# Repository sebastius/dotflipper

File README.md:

# dotflipper

My Flip Dot controller.

## Status (November 2026)

- **v1** (`hardware-v1`): the original controller, based on the PCA9685 i2c port expanders. Tested and
  working, but dangerous and slow.
- **v3** (`hardware-v3`): a new controller with 74HC595 shift registers, where the hardware keeps plus and
  minus of a wire apart. Designed and on order, not tested yet.
- **Software** (`software`): firmware for v1 and v3, being developed with the help of AI. Try the v3
  firmware in your browser: https://sebastius.github.io/dotflipper/
- **Original software** (`software-original`): the hand-written firmware from 2018-2020, heavily outdated.

## License

CC BY-SA 4.0, except the word clock font derived from Ithaca, which stays under the SIL Open Font License.
Fonts, authors and licenses: [software/tools/fonts](software/tools/fonts/README.md).

lol

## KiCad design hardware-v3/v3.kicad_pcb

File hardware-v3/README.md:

# Controller v3

> **Untested.** The schematic, placement, scripts and part choices were made with an AI assistant
> (Claude); the board was routed by hand in KiCad. The board passes DRC, but none has been built yet.
> Test the first board with a current-limited supply: these drivers switch 20 V coils, and a mistake
> can short them.

One flip dot panel of 32x16 (32 lines on X1, 16 rows on X2/X3) per board, so two boards for a 32x32
display. 205 x 80 mm, two layers, all logic and drivers SMD.

## How it works

- **Drivers:** six groups of eight lines. Each group has two 74HC595s on the same data, one feeding an
  XL62783 (lines to 20 V) and one feeding a ULN2803A (lines to ground). Groups 1-4 drive the 32 lines on
  X1, group 5 rows 0-7 on X3, group 6 rows 8-15 on X2. `bits.csv` lists which bit drives which wire.
- **Protection:** DIR_X1, DIR_ROW and nOE gate the output enables of the 595s through a 74HC32 and
  74HC14, so plus and minus of one line or row can never be on together, also not after a software bug.
  Change DIR only while nOE is high.
- **Chain:** boards chain over a 10-way flat cable, J2 of one board to J3 of the next. Each board
  buffers the incoming signals with a 74AHCT541 (TTL inputs, so the 3.3 V of the ESP32 is enough), and
  the chain data leaves through a 74LVC1G79 on the falling SCLK edge. Close JP1 on the last board: the
  chain data then returns over RET to the ESP32 (IO13, through R4/R5 to 3.3 V) so the firmware can read
  the chain back.
- **ESP32:** one ESP32-S3-DevKitC-1 (A1) drives all boards; on the other boards A1 stays empty.
  DATA IO11, SCLK IO12, LATCH IO10, nOE IO9, DIR_X1 IO14, DIR_ROW IO8, return IO13, coil current IO4.
- **Coil current:** all ULN2803As return to ground through a 0.1 ohm shunt (R8). An INA180A2 measures
  it; R6/R7 scale 0.45 A to 1.5 V for IO4. TP1 brings the same signal out on boards without an ESP32.
- **Power:** 20 V in on J4, J5 passes it on to the next board. 3 A fuse F1, 220 uF bulk capacitor C15.
  An AP63205 buck makes 5 V for the logic and, through D1, for the ESP32 (D1 keeps USB power on the
  ESP32 from feeding the board).

## Files

- `generate.py`: makes the schematic and brings the board up to date; placement and tracks stay.
  `--opnieuw` throws the board away and places everything again.
- `export_jlc.py`: Gerbers, drill files, BOM and CPL for JLCPCB in `jlcpcb/`. It refuses to run while
  DRC finds errors, open connections or differences with the schematic.
- `jlcpcb/`: the production files of the current board. Through-hole parts (connectors, headers,
  terminals, the ESP32) are not in the BOM; order and solder them yourself.
- `v3.kicad_dru`: design rules for JLCPCB standard 2-layer 1 oz boards.
- `bits.csv`: which bit of the chain drives which wire, for the firmware.

## Not yet verified on hardware

- Coil peak current: estimated 450-480 mA, the drivers are rated 390-400 mA recommended, 500 mA absolute.
- The ESP32 footprint: print it 1:1 and lay the module on it, clones are not always the same.
- The buck regulator layout.
- The part rotations in the CPL, checked only in the JLC preview.

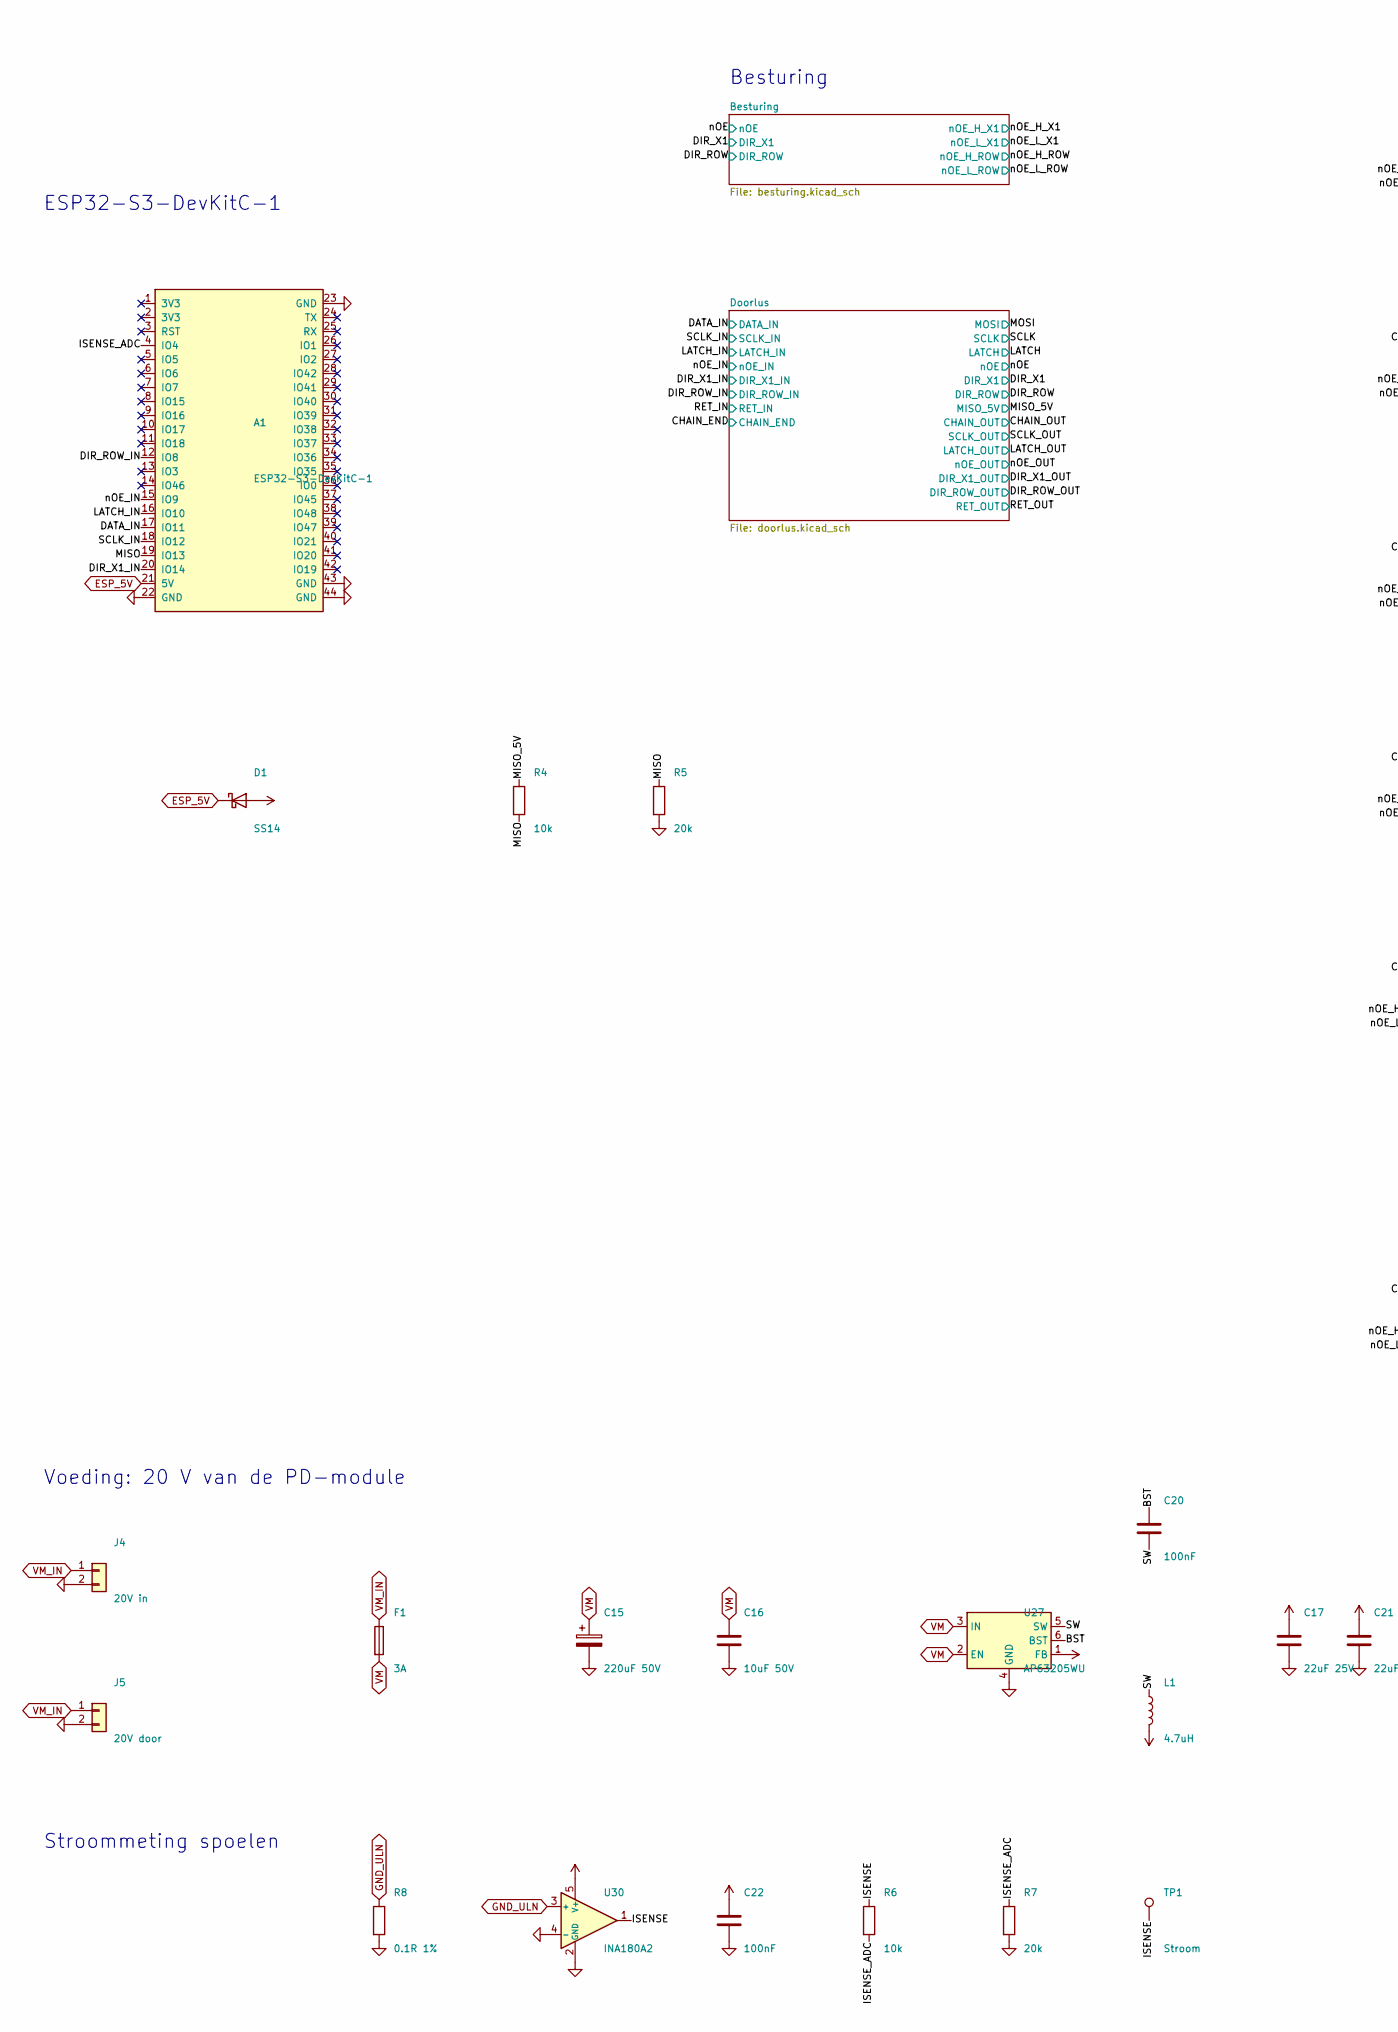
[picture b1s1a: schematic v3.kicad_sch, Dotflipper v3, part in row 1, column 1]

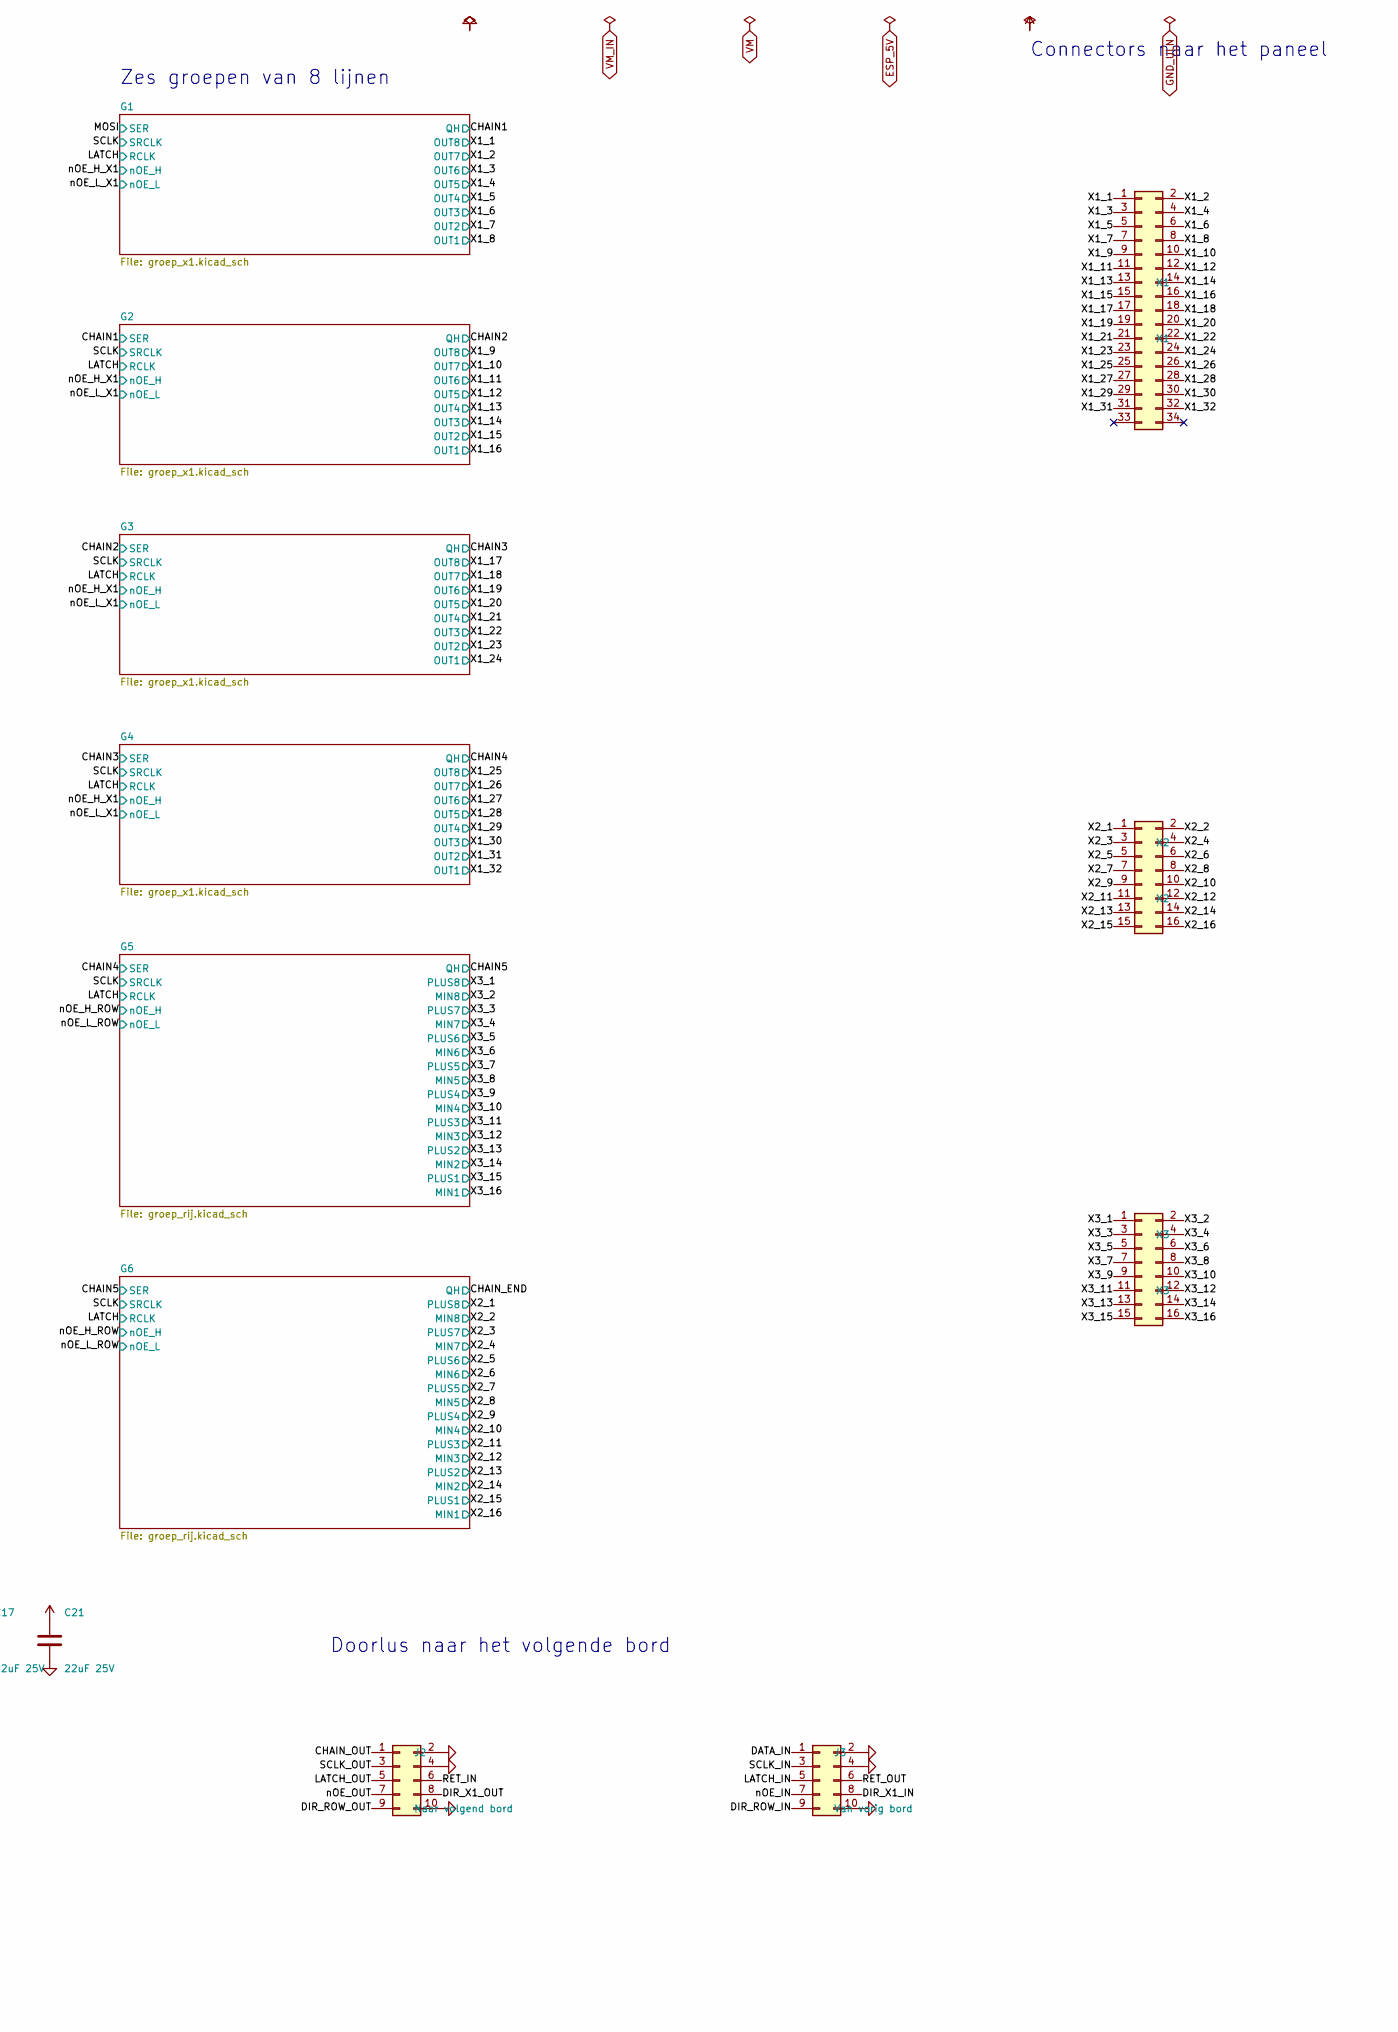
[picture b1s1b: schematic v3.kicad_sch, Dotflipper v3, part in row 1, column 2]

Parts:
A1: ESP32-S3-DevKitC-1
C15: 220uF 50V; CP_Elec_10x10.5; LCSC C46550417
C16: 10uF 50V; C_1206_3216Metric; LCSC C13585
C17, C21: 22uF 25V; C_1206_3216Metric; LCSC C12891
C20, C22: 100nF; C_0603_1608Metric; LCSC C14663
D1: SS14; D_SMA; LCSC C2480
F1: 3A; Fuse_1206_3216Metric; LCSC C182445
J2: Naar volgend bord; IDC-Header_2x05_P2.54mm_Vertical
J3: Van vorig bord; IDC-Header_2x05_P2.54mm_Vertical
J4: 20V in; TerminalBlock_Phoenix_MKDS-1,5-2-5.08_1x02_P5.08mm_Horizont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
J5: 20V door; TerminalBlock_Phoenix_MKDS-1,5-2-5.08_1x02_P5.08mm_Horizont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
L1: 4.7uH; L_Sunlord_SWPA4030S; LCSC C57269
R4, R6: 10k; R_0603_1608Metric; LCSC C25804
R5, R7: 20k; R_0603_1608Metric; LCSC C4184
R8: 0.1R 1%; R_1206_3216Metric; LCSC C25334
TP1: Stroom; TestPoint_Pad_D1.5mm
U27: AP63205WU; TSOT-23-6; LCSC C2071056
U30: INA180A2; SOT-23-5; LCSC C192764
X1: X1; IDC-Header_2x17_P2.54mm_Vertical
X2: X2; IDC-Header_2x08_P2.54mm_Vertical
X3: X3; IDC-Header_2x08_P2.54mm_Vertical

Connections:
+5V: C17.1, C21.1, C22.1, D1.2 (A), L1.2, U27.1 (FB), U30.5 (V+); also elsewhere on the board
/BST: C20.1, U27.6 (BST)
/CHAIN_OUT: J2.1; also elsewhere on the board
/DATA_IN: A1.17 (IO11), J3.1; also elsewhere on the board
/DIR_ROW_IN: A1.12 (IO8), J3.9; also elsewhere on the board
/DIR_ROW_OUT: J2.9; also elsewhere on the board
/DIR_X1_IN: A1.20 (IO14), J3.8; also elsewhere on the board
/DIR_X1_OUT: J2.8; also elsewhere on the board
/ISENSE: R6.1, TP1.1, U30.1
/ISENSE_ADC: A1.4 (IO4), R6.2, R7.1
/LATCH_IN: A1.16 (IO10), J3.5; also elsewhere on the board
/LATCH_OUT: J2.5; also elsewhere on the board
/MISO: A1.19 (IO13), R4.2, R5.1
/MISO_5V: R4.1; also elsewhere on the board
/RET_IN: J2.6; also elsewhere on the board
/RET_OUT: J3.6; also elsewhere on the board
/SCLK_IN: A1.18 (IO12), J3.3; also elsewhere on the board
/SCLK_OUT: J2.3; also elsewhere on the board
/SW: C20.2, L1.1, U27.5 (SW)
/X1_1: X1.1; also elsewhere on the board
/X1_2: X1.2; also elsewhere on the board
/X1_3: X1.3; also elsewhere on the board
/X1_4: X1.4; also elsewhere on the board
/X1_5: X1.5; also elsewhere on the board
/X1_6: X1.6; also elsewhere on the board
/X1_7: X1.7; also elsewhere on the board
/X1_8: X1.8; also elsewhere on the board
/X1_9: X1.9; also elsewhere on the board
/X1_10: X1.10; also elsewhere on the board
/X1_11: X1.11; also elsewhere on the board
/X1_12: X1.12; also elsewhere on the board
/X1_13: X1.13; also elsewhere on the board
/X1_14: X1.14; also elsewhere on the board
/X1_15: X1.15; also elsewhere on the board
/X1_16: X1.16; also elsewhere on the board
/X1_17: X1.17; also elsewhere on the board
/X1_18: X1.18; also elsewhere on the board
/X1_19: X1.19; also elsewhere on the board
/X1_20: X1.20; also elsewhere on the board
/X1_21: X1.21; also elsewhere on the board
/X1_22: X1.22; also elsewhere on the board
/X1_23: X1.23; also elsewhere on the board
/X1_24: X1.24; also elsewhere on the board
/X1_25: X1.25; also elsewhere on the board
/X1_26: X1.26; also elsewhere on the board
/X1_27: X1.27; also elsewhere on the board
/X1_28: X1.28; also elsewhere on the board
/X1_29: X1.29; also elsewhere on the board
/X1_30: X1.30; also elsewhere on the board
/X1_31: X1.31; also elsewhere on the board
/X1_32: X1.32; also elsewhere on the board
/X2_1: X2.1; also elsewhere on the board
/X2_2: X2.2; also elsewhere on the board
/X2_3: X2.3; also elsewhere on the board
/X2_4: X2.4; also elsewhere on the board
/X2_5: X2.5; also elsewhere on the board
/X2_6: X2.6; also elsewhere on the board
/X2_7: X2.7; also elsewhere on the board
/X2_8: X2.8; also elsewhere on the board
/X2_9: X2.9; also elsewhere on the board
/X2_10: X2.10; also elsewhere on the board
/X2_11: X2.11; also elsewhere on the board
/X2_12: X2.12; also elsewhere on the board
/X2_13: X2.13; also elsewhere on the board
/X2_14: X2.14; also elsewhere on the board
/X2_15: X2.15; also elsewhere on the board
/X2_16: X2.16; also elsewhere on the board
/X3_1: X3.1; also elsewhere on the board
/X3_2: X3.2; also elsewhere on the board
/X3_3: X3.3; also elsewhere on the board
/X3_4: X3.4; also elsewhere on the board
/X3_5: X3.5; also elsewhere on the board
/X3_6: X3.6; also elsewhere on the board
/X3_7: X3.7; also elsewhere on the board
/X3_8: X3.8; also elsewhere on the board
/X3_9: X3.9; also elsewhere on the board
/X3_10: X3.10; also elsewhere on the board
/X3_11: X3.11; also elsewhere on the board
/X3_12: X3.12; also elsewhere on the board
/X3_13: X3.13; also elsewhere on the board
/X3_14: X3.14; also elsewhere on the board
/X3_15: X3.15; also elsewhere on the board
/X3_16: X3.16; also elsewhere on the board
/nOE_IN: A1.15 (IO9), J3.7; also elsewhere on the board
/nOE_OUT: J2.7; also elsewhere on the board
ESP_5V: A1.21 (5V), D1.1 (K)
GND: A1.22 (GND), A1.23 (GND), A1.43 (GND), A1.44 (GND), C15.2, C16.2, C17.2, C21.2, C22.2, J2.2, J2.4, J2.10, J3.2, J3.4, J3.10, J4.2, J5.2, R5.2, R7.2, R8.2, U27.4 (GND), U30.2 (GND), U30.4 (-); also elsewhere on the board
GND_ULN: R8.1, U30.3 (+); also elsewhere on the board
VM: C15.1, C16.1, F1.2, U27.2 (EN), U27.3 (IN); also elsewhere on the board
VM_IN: F1.1, J4.1, J5.1

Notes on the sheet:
ESP32-S3-DevKitC-1
Voeding: 20 V van de PD-module
Stroommeting spoelen
Doorlus naar het volgende bord
Besturing
Zes groepen van 8 lijnen
Connectors naar het paneel

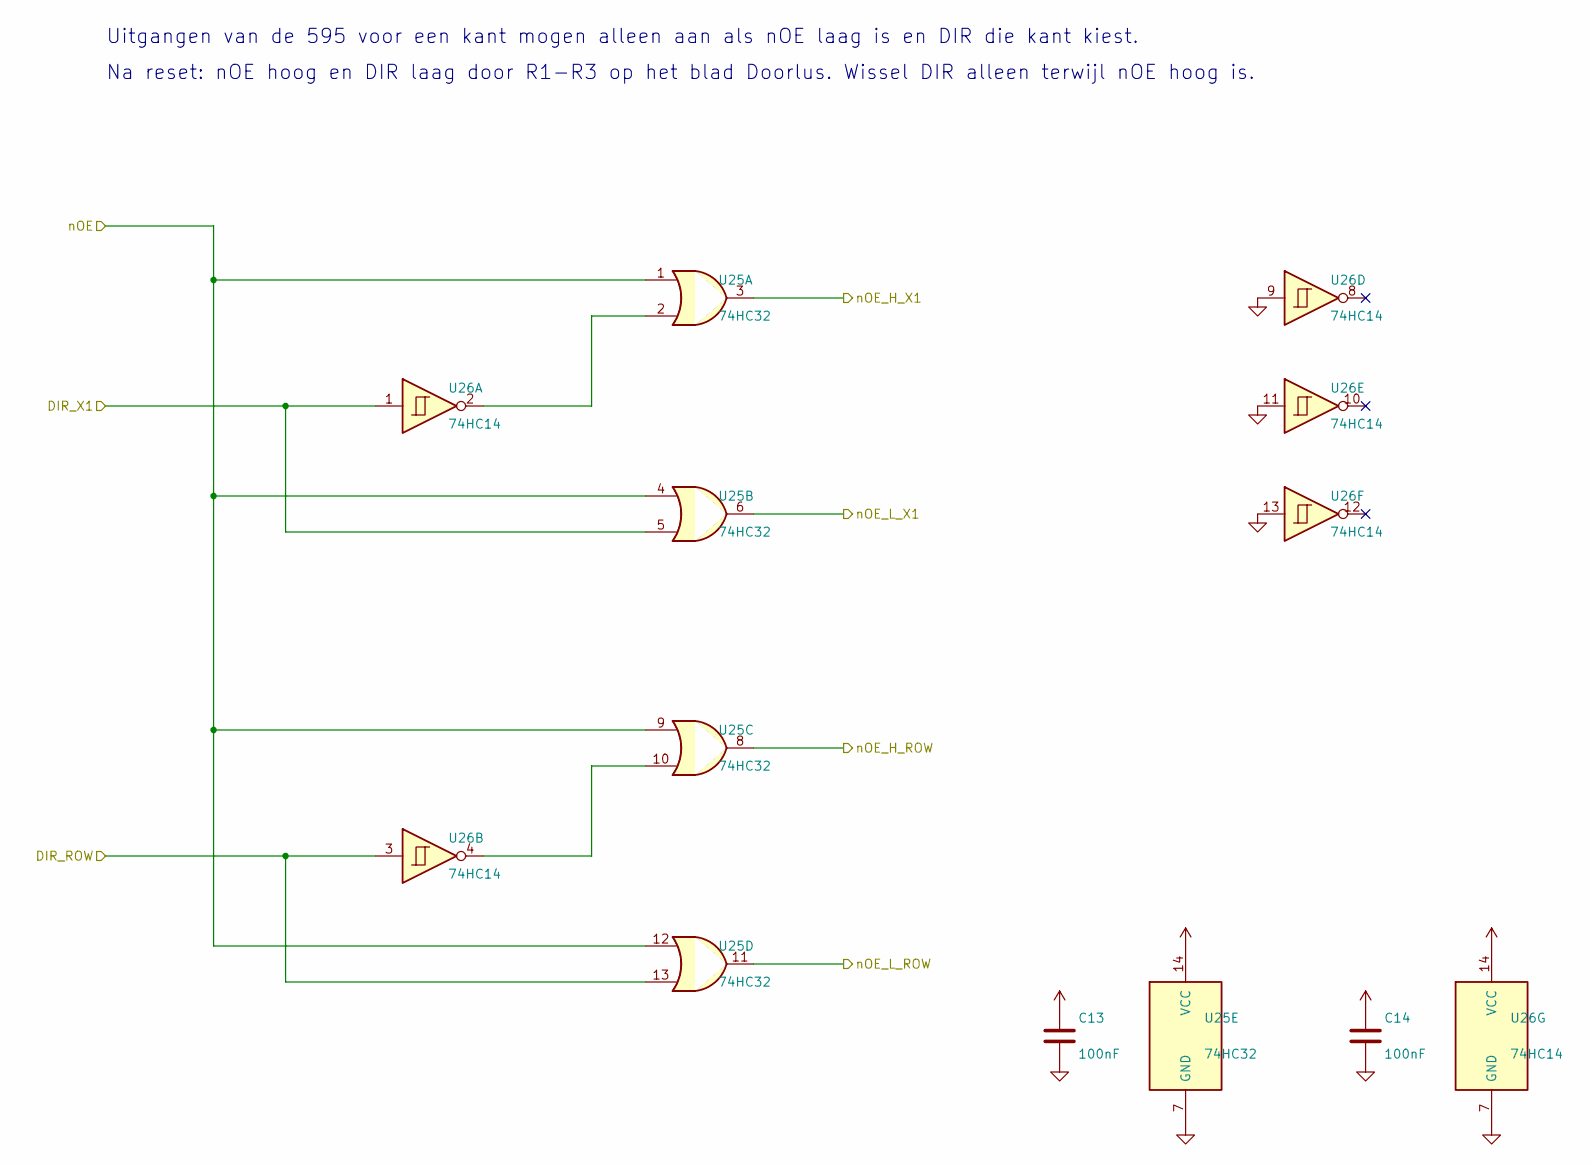
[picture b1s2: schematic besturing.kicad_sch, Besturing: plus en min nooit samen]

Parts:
C13, C14: 100nF; C_0603_1608Metric; LCSC C14663
U25: 74HC32; SOIC-14_3.9x8.7mm_P1.27mm; LCSC C5632
U26: 74HC14; SOIC-14_3.9x8.7mm_P1.27mm; LCSC C5605

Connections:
+5V: C13.1, C14.1, U25.14 (VCC), U26.14 (VCC); also elsewhere on the board
/DIR_ROW: U25.13, U26.3; also elsewhere on the board
/DIR_X1: U25.5, U26.1; also elsewhere on the board
/nOE: U25.1, U25.4, U25.9, U25.12; also elsewhere on the board
/nOE_H_ROW: U25.8; also elsewhere on the board
/nOE_H_X1: U25.3; also elsewhere on the board
/nOE_L_ROW: U25.11; also elsewhere on the board
/nOE_L_X1: U25.6; also elsewhere on the board
GND: C13.2, C14.2, U25.7 (GND), U26.7 (GND), U26.9, U26.11, U26.13; also elsewhere on the board
unnamed: U25.2, U26.2
unnamed: U25.10, U26.4

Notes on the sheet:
Uitgangen van de 595 voor een kant mogen alleen aan als nOE laag is en DIR die kant kiest.
Na reset: nOE hoog en DIR laag door R1-R3 op het blad Doorlus. Wissel DIR alleen terwijl nOE hoog is.

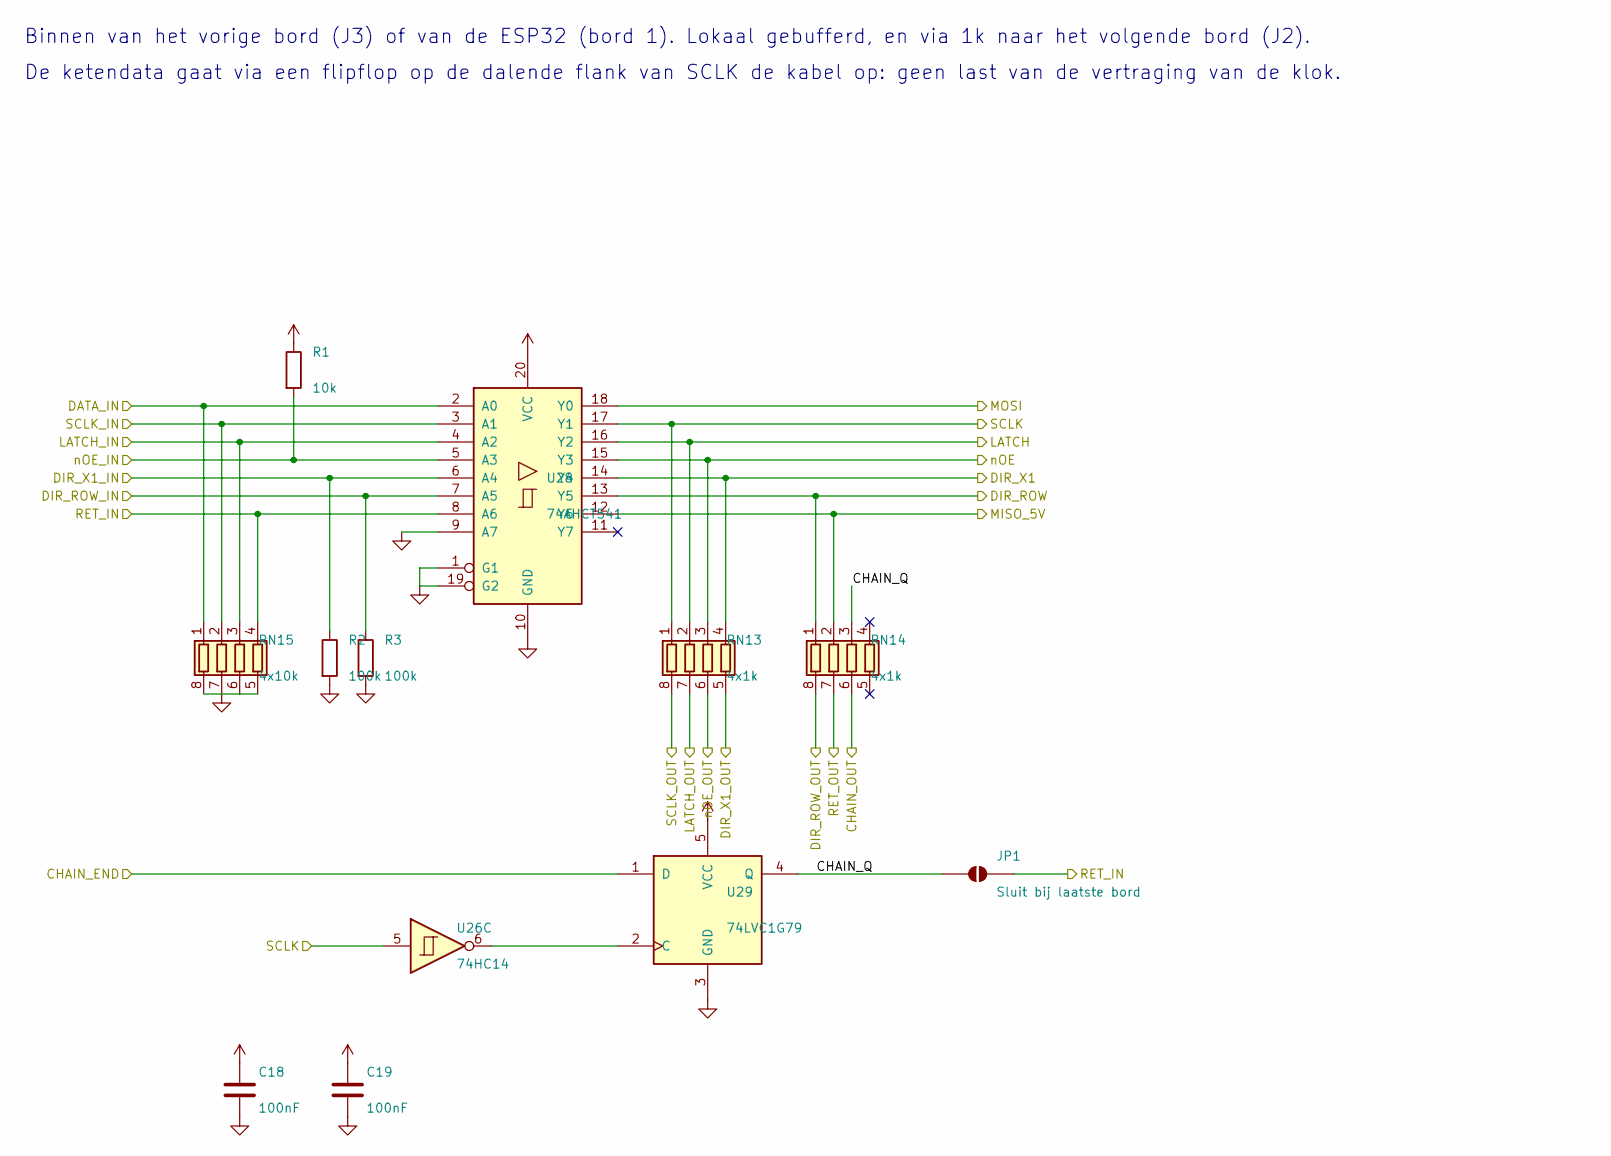
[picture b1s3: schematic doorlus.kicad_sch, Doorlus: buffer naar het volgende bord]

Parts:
C18, C19: 100nF; C_0603_1608Metric; LCSC C14663
JP1: Sluit bij laatste bord; SolderJumper-2_P1.3mm_Open_TrianglePad1.0x1.5mm
R1: 10k; R_0603_1608Metric; LCSC C25804
R2, R3: 100k; R_0603_1608Metric; LCSC C25803
RN13, RN14: 4x1k; R_Array_Convex_4x0603; LCSC C20197
RN15: 4x10k; R_Array_Convex_4x0603; LCSC C29718
U26: 74HC14; SOIC-14_3.9x8.7mm_P1.27mm; LCSC C5605
U28: 74AHCT541; SOIC-20W_7.5x12.8mm_P1.27mm; LCSC C2682058
U29: 74LVC1G79; SOT-23-5; LCSC C42878

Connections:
+5V: C18.1, C19.1, R1.1, U28.20 (VCC), U29.5 (VCC); also elsewhere on the board
/CHAIN_END: U29.1 (D); also elsewhere on the board
/CHAIN_OUT: RN14.6 (R3.2); also elsewhere on the board
/DATA_IN: RN15.1 (R1.1), U28.2 (A0); also elsewhere on the board
/DIR_ROW: RN14.1 (R1.1), U28.13 (Y5); also elsewhere on the board
/DIR_ROW_IN: R3.1, U28.7 (A5); also elsewhere on the board
/DIR_ROW_OUT: RN14.8 (R1.2); also elsewhere on the board
/DIR_X1: RN13.4 (R4.1), U28.14 (Y4); also elsewhere on the board
/DIR_X1_IN: R2.1, U28.6 (A4); also elsewhere on the board
/DIR_X1_OUT: RN13.5 (R4.2); also elsewhere on the board
/Doorlus/CHAIN_Q: JP1.1 (A), RN14.3 (R3.1), U29.4 (Q)
/LATCH: RN13.2 (R2.1), U28.16 (Y2); also elsewhere on the board
/LATCH_IN: RN15.3 (R3.1), U28.4 (A2); also elsewhere on the board
/LATCH_OUT: RN13.7 (R2.2); also elsewhere on the board
/MISO_5V: RN14.2 (R2.1), U28.12 (Y6); also elsewhere on the board
/MOSI: U28.18 (Y0); also elsewhere on the board
/RET_IN: JP1.2 (B), RN15.4 (R4.1), U28.8 (A6); also elsewhere on the board
/RET_OUT: RN14.7 (R2.2); also elsewhere on the board
/SCLK: RN13.1 (R1.1), U26.5, U28.17 (Y1); also elsewhere on the board
/SCLK_IN: RN15.2 (R2.1), U28.3 (A1); also elsewhere on the board
/SCLK_OUT: RN13.8 (R1.2); also elsewhere on the board
/nOE: RN13.3 (R3.1), U28.15 (Y3); also elsewhere on the board
/nOE_IN: R1.2, U28.5 (A3); also elsewhere on the board
/nOE_OUT: RN13.6 (R3.2); also elsewhere on the board
GND: C18.2, C19.2, R2.2, R3.2, RN15.5 (R4.2), RN15.6 (R3.2), RN15.7 (R2.2), RN15.8 (R1.2), U28.1 (G1), U28.9 (A7), U28.10 (GND), U28.19 (G2), U29.3 (GND); also elsewhere on the board
unnamed: U26.6, U29.2 (C)

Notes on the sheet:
Binnen van het vorige bord (J3) of van de ESP32 (bord 1). Lokaal gebufferd, en via 1k naar het volgende bord (J2).
De ketendata gaat via een flipflop op de dalende flank van SCLK de kabel op: geen last van de vertraging van de klok.

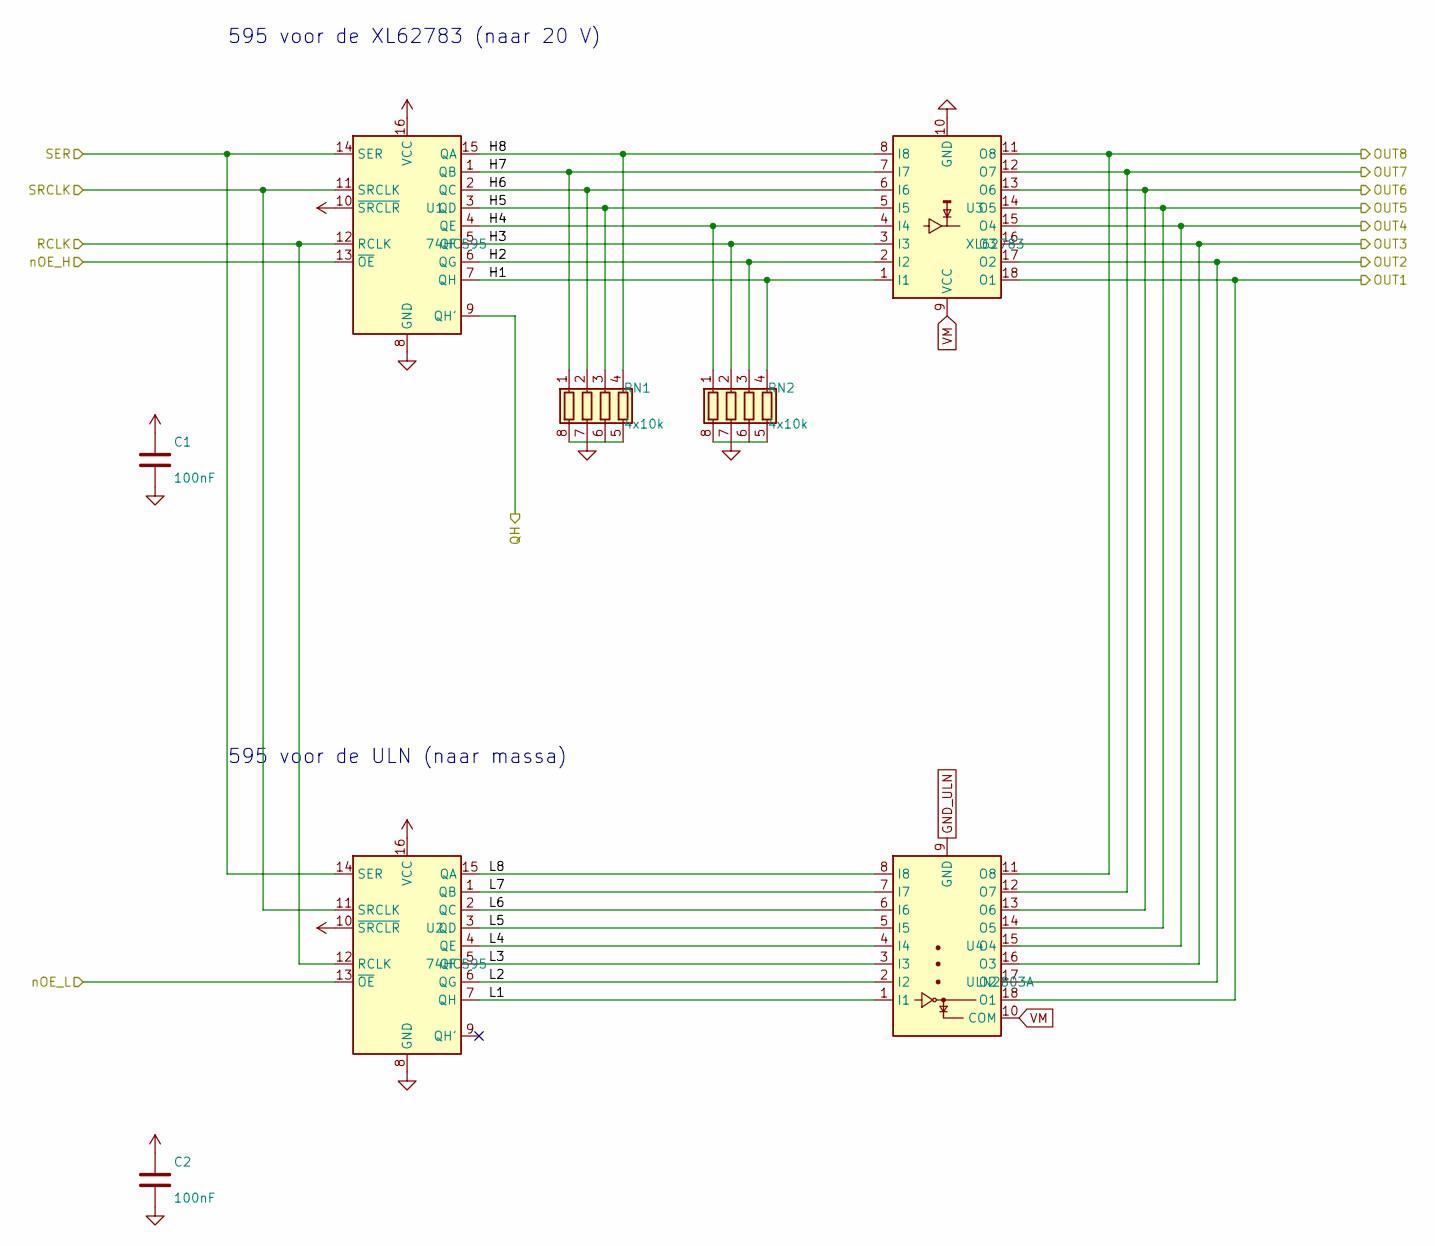
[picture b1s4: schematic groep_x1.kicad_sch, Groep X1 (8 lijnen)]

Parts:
C1, C2: 100nF; C_0603_1608Metric; LCSC C14663
RN1, RN2: 4x10k; R_Array_Convex_4x0603; LCSC C29718
U1, U2: 74HC595; SOIC-16_3.9x9.9mm_P1.27mm; LCSC C5947
U3: XL62783; SOIC-18W_7.5x11.6mm_P1.27mm; LCSC C556260
U4: ULN2803A; SOIC-18W_7.5x11.6mm_P1.27mm; LCSC C845537

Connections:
+5V: C1.1, C2.1, U1.10 (~SRCLR), U1.16 (VCC), U2.10 (~SRCLR), U2.16 (VCC); also elsewhere on the board
/CHAIN1: U1.9 (QH'); also elsewhere on the board
/G1/H1: RN2.4 (R4.1), U1.7 (QH), U3.1 (I1)
/G1/H2: RN2.3 (R3.1), U1.6 (QG), U3.2 (I2)
/G1/H3: RN2.2 (R2.1), U1.5 (QF), U3.3 (I3)
/G1/H4: RN2.1 (R1.1), U1.4 (QE), U3.4 (I4)
/G1/H5: RN1.3 (R3.1), U1.3 (QD), U3.5 (I5)
/G1/H6: RN1.2 (R2.1), U1.2 (QC), U3.6 (I6)
/G1/H7: RN1.1 (R1.1), U1.1 (QB), U3.7 (I7)
/G1/H8: RN1.4 (R4.1), U1.15 (QA), U3.8 (I8)
/G1/L1: U2.7 (QH), U4.1 (I1)
/G1/L2: U2.6 (QG), U4.2 (I2)
/G1/L3: U2.5 (QF), U4.3 (I3)
/G1/L4: U2.4 (QE), U4.4 (I4)
/G1/L5: U2.3 (QD), U4.5 (I5)
/G1/L6: U2.2 (QC), U4.6 (I6)
/G1/L7: U2.1 (QB), U4.7 (I7)
/G1/L8: U2.15 (QA), U4.8 (I8)
/LATCH: U1.12 (RCLK), U2.12 (RCLK); also elsewhere on the board
/MOSI: U1.14 (SER), U2.14 (SER); also elsewhere on the board
/SCLK: U1.11 (SRCLK), U2.11 (SRCLK); also elsewhere on the board
/X1_1: U3.11 (O8), U4.11 (O8); also elsewhere on the board
/X1_2: U3.12 (O7), U4.12 (O7); also elsewhere on the board
/X1_3: U3.13 (O6), U4.13 (O6); also elsewhere on the board
/X1_4: U3.14 (O5), U4.14 (O5); also elsewhere on the board
/X1_5: U3.15 (O4), U4.15 (O4); also elsewhere on the board
/X1_6: U3.16 (O3), U4.16 (O3); also elsewhere on the board
/X1_7: U3.17 (O2), U4.17 (O2); also elsewhere on the board
/X1_8: U3.18 (O1), U4.18 (O1); also elsewhere on the board
/nOE_H_X1: U1.13 (~OE); also elsewhere on the board
/nOE_L_X1: U2.13 (~OE); also elsewhere on the board
GND: C1.2, C2.2, RN1.5 (R4.2), RN1.6 (R3.2), RN1.7 (R2.2), RN1.8 (R1.2), RN2.5 (R4.2), RN2.6 (R3.2), RN2.7 (R2.2), RN2.8 (R1.2), U1.8 (GND), U2.8 (GND), U3.10 (GND); also elsewhere on the board
GND_ULN: U4.9 (GND); also elsewhere on the board
VM: U3.9 (VCC), U4.10 (COM); also elsewhere on the board

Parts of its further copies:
C3, C4, C5, C6, C7, C8: 100nF; C_0603_1608Metric; LCSC C14663
RN3, RN4, RN5, RN6, RN7, RN8: 4x10k; R_Array_Convex_4x0603; LCSC C29718
U5, U6, U9, U10, U13, U14: 74HC595; SOIC-16_3.9x9.9mm_P1.27mm; LCSC C5947
U7, U11, U15: XL62783; SOIC-18W_7.5x11.6mm_P1.27mm; LCSC C556260
U8, U12, U16: ULN2803A; SOIC-18W_7.5x11.6mm_P1.27mm; LCSC C845537

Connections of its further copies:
+5V: C3.1, C4.1, C5.1, C6.1, C7.1, C8.1, U5.10 (~SRCLR), U5.16 (VCC), U6.10 (~SRCLR), U6.16 (VCC), U9.10 (~SRCLR), U9.16 (VCC), U10.10 (~SRCLR), U10.16 (VCC), U13.10 (~SRCLR), U13.16 (VCC), U14.10 (~SRCLR), U14.16 (VCC); also elsewhere on the board
/CHAIN1: U5.14 (SER), U6.14 (SER); also elsewhere on the board
/CHAIN2: U5.9 (QH'), U9.14 (SER), U10.14 (SER)
/CHAIN3: U9.9 (QH'), U13.14 (SER), U14.14 (SER)
/CHAIN4: U13.9 (QH'); also elsewhere on the board
/G2/H1: RN4.4 (R4.1), U5.7 (QH), U7.1 (I1)
/G2/H2: RN4.3 (R3.1), U5.6 (QG), U7.2 (I2)
/G2/H3: RN4.2 (R2.1), U5.5 (QF), U7.3 (I3)
/G2/H4: RN4.1 (R1.1), U5.4 (QE), U7.4 (I4)
/G2/H5: RN3.3 (R3.1), U5.3 (QD), U7.5 (I5)
/G2/H6: RN3.2 (R2.1), U5.2 (QC), U7.6 (I6)
/G2/H7: RN3.1 (R1.1), U5.1 (QB), U7.7 (I7)
/G2/H8: RN3.4 (R4.1), U5.15 (QA), U7.8 (I8)
/G2/L1: U6.7 (QH), U8.1 (I1)
/G2/L2: U6.6 (QG), U8.2 (I2)
/G2/L3: U6.5 (QF), U8.3 (I3)
/G2/L4: U6.4 (QE), U8.4 (I4)
/G2/L5: U6.3 (QD), U8.5 (I5)
/G2/L6: U6.2 (QC), U8.6 (I6)
/G2/L7: U6.1 (QB), U8.7 (I7)
/G2/L8: U6.15 (QA), U8.8 (I8)
/G3/H1: RN6.4 (R4.1), U9.7 (QH), U11.1 (I1)
/G3/H2: RN6.3 (R3.1), U9.6 (QG), U11.2 (I2)
/G3/H3: RN6.2 (R2.1), U9.5 (QF), U11.3 (I3)
/G3/H4: RN6.1 (R1.1), U9.4 (QE), U11.4 (I4)
/G3/H5: RN5.3 (R3.1), U9.3 (QD), U11.5 (I5)
/G3/H6: RN5.2 (R2.1), U9.2 (QC), U11.6 (I6)
/G3/H7: RN5.1 (R1.1), U9.1 (QB), U11.7 (I7)
/G3/H8: RN5.4 (R4.1), U9.15 (QA), U11.8 (I8)
/G3/L1: U10.7 (QH), U12.1 (I1)
/G3/L2: U10.6 (QG), U12.2 (I2)
/G3/L3: U10.5 (QF), U12.3 (I3)
/G3/L4: U10.4 (QE), U12.4 (I4)
/G3/L5: U10.3 (QD), U12.5 (I5)
/G3/L6: U10.2 (QC), U12.6 (I6)
/G3/L7: U10.1 (QB), U12.7 (I7)
/G3/L8: U10.15 (QA), U12.8 (I8)
/G4/H1: RN8.4 (R4.1), U13.7 (QH), U15.1 (I1)
/G4/H2: RN8.3 (R3.1), U13.6 (QG), U15.2 (I2)
/G4/H3: RN8.2 (R2.1), U13.5 (QF), U15.3 (I3)
/G4/H4: RN8.1 (R1.1), U13.4 (QE), U15.4 (I4)
/G4/H5: RN7.3 (R3.1), U13.3 (QD), U15.5 (I5)
/G4/H6: RN7.2 (R2.1), U13.2 (QC), U15.6 (I6)
/G4/H7: RN7.1 (R1.1), U13.1 (QB), U15.7 (I7)
/G4/H8: RN7.4 (R4.1), U13.15 (QA), U15.8 (I8)
/G4/L1: U14.7 (QH), U16.1 (I1)
/G4/L2: U14.6 (QG), U16.2 (I2)
/G4/L3: U14.5 (QF), U16.3 (I3)
/G4/L4: U14.4 (QE), U16.4 (I4)
/G4/L5: U14.3 (QD), U16.5 (I5)
/G4/L6: U14.2 (QC), U16.6 (I6)
/G4/L7: U14.1 (QB), U16.7 (I7)
/G4/L8: U14.15 (QA), U16.8 (I8)
/LATCH: U5.12 (RCLK), U6.12 (RCLK), U9.12 (RCLK), U10.12 (RCLK), U13.12 (RCLK), U14.12 (RCLK); also elsewhere on the board
/SCLK: U5.11 (SRCLK), U6.11 (SRCLK), U9.11 (SRCLK), U10.11 (SRCLK), U13.11 (SRCLK), U14.11 (SRCLK); also elsewhere on the board
/X1_9: U7.11 (O8), U8.11 (O8); also elsewhere on the board
/X1_10: U7.12 (O7), U8.12 (O7); also elsewhere on the board
/X1_11: U7.13 (O6), U8.13 (O6); also elsewhere on the board
/X1_12: U7.14 (O5), U8.14 (O5); also elsewhere on the board
/X1_13: U7.15 (O4), U8.15 (O4); also elsewhere on the board
/X1_14: U7.16 (O3), U8.16 (O3); also elsewhere on the board
/X1_15: U7.17 (O2), U8.17 (O2); also elsewhere on the board
/X1_16: U7.18 (O1), U8.18 (O1); also elsewhere on the board
/X1_17: U11.11 (O8), U12.11 (O8); also elsewhere on the board
/X1_18: U11.12 (O7), U12.12 (O7); also elsewhere on the board
/X1_19: U11.13 (O6), U12.13 (O6); also elsewhere on the board
/X1_20: U11.14 (O5), U12.14 (O5); also elsewhere on the board
/X1_21: U11.15 (O4), U12.15 (O4); also elsewhere on the board
/X1_22: U11.16 (O3), U12.16 (O3); also elsewhere on the board
/X1_23: U11.17 (O2), U12.17 (O2); also elsewhere on the board
/X1_24: U11.18 (O1), U12.18 (O1); also elsewhere on the board
/X1_25: U15.11 (O8), U16.11 (O8); also elsewhere on the board
/X1_26: U15.12 (O7), U16.12 (O7); also elsewhere on the board
/X1_27: U15.13 (O6), U16.13 (O6); also elsewhere on the board
/X1_28: U15.14 (O5), U16.14 (O5); also elsewhere on the board
/X1_29: U15.15 (O4), U16.15 (O4); also elsewhere on the board
/X1_30: U15.16 (O3), U16.16 (O3); also elsewhere on the board
/X1_31: U15.17 (O2), U16.17 (O2); also elsewhere on the board
/X1_32: U15.18 (O1), U16.18 (O1); also elsewhere on the board
/nOE_H_X1: U5.13 (~OE), U9.13 (~OE), U13.13 (~OE); also elsewhere on the board
/nOE_L_X1: U6.13 (~OE), U10.13 (~OE), U14.13 (~OE); also elsewhere on the board
GND: C3.2, C4.2, C5.2, C6.2, C7.2, C8.2, RN3.5 (R4.2), RN3.6 (R3.2), RN3.7 (R2.2), RN3.8 (R1.2), RN4.5 (R4.2), RN4.6 (R3.2), RN4.7 (R2.2), RN4.8 (R1.2), RN5.5 (R4.2), RN5.6 (R3.2), RN5.7 (R2.2), RN5.8 (R1.2), RN6.5 (R4.2), RN6.6 (R3.2), RN6.7 (R2.2), RN6.8 (R1.2), RN7.5 (R4.2), RN7.6 (R3.2), RN7.7 (R2.2), RN7.8 (R1.2), RN8.5 (R4.2), RN8.6 (R3.2), RN8.7 (R2.2), RN8.8 (R1.2), U5.8 (GND), U6.8 (GND), U7.10 (GND), U9.8 (GND), U10.8 (GND), U11.10 (GND), U13.8 (GND), U14.8 (GND), U15.10 (GND); also elsewhere on the board
GND_ULN: U8.9 (GND), U12.9 (GND), U16.9 (GND); also elsewhere on the board
VM: U7.9 (VCC), U8.10 (COM), U11.9 (VCC), U12.10 (COM), U15.9 (VCC), U16.10 (COM); also elsewhere on the board

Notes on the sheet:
595 voor de XL62783 (naar 20 V)
595 voor de ULN (naar massa)
